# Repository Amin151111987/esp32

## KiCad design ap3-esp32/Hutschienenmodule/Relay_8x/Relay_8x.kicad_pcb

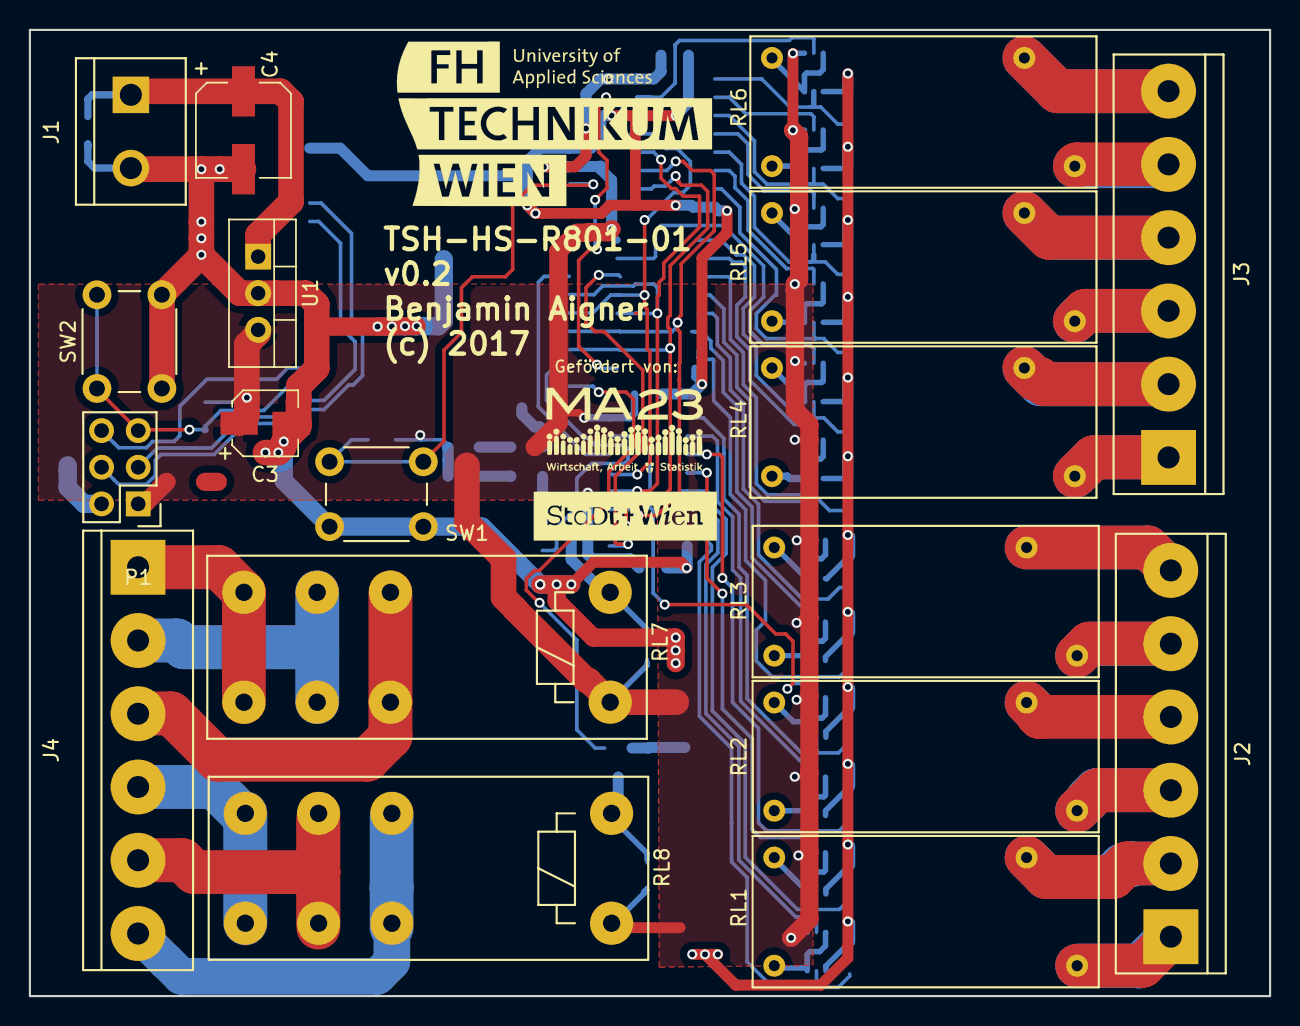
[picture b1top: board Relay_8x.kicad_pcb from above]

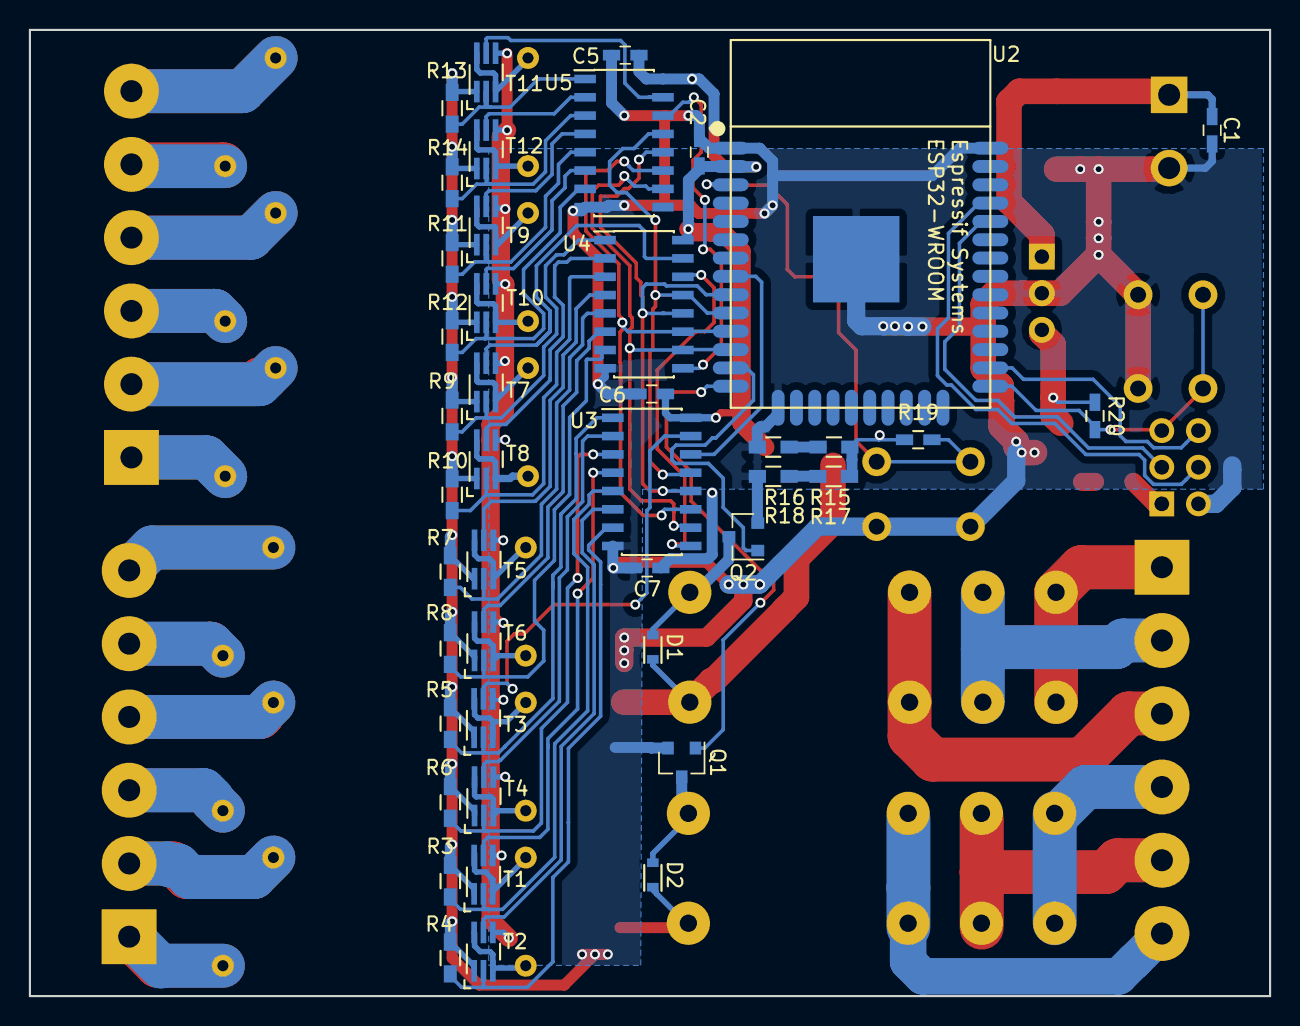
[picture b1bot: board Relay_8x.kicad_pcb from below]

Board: 2 copper layers, 86.0 x 67.0 mm, 61 parts (43 on the bottom side), 75 nets.

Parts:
C1, C2, C5, C6, C7: 100nF; C_0603_HandSoldering
C3: 22uF; CP_Elec_4x5.7
C4: 10uF; CP_Elec_6.3x5.8
D1, D2: D; D_0603
J1: Screw_Terminal_1x02; bornier2
J2, J3, J4: Screw_Terminal_1x06; bornier6
P1: CONN_02X03; Pin_Header_Straight_2x03
Q1, Q2: MMBF170; SOT-23
R3, R4, R5, R6, R7, R8, R9, R10, R11, R12, R13, R14: R_Small; R_0603_HandSoldering
R15, R16, R17, R18: R; R_0603_HandSoldering
R19, R20: 10k; C_0603_HandSoldering
RL1, RL2, RL3, RL4, RL5, RL6: ADW1103; ADW11
RL7, RL8: OZ-SS-103LM1; Relay_SPDT_Schrack-RT1_RM5mm
SW1, SW2: SW_Push; SW_PUSH_6mm_h7.3mm
T1, T2, T3, T4, T5, T6, T7, T8, T9, T10, T11, T12: NX3008CBKS; SC-70-6_Handsoldering
U1: TR10S3V3; TO-220_Vertical
U2: ESP32-WROOM
U3, U4, U5: 74HC595; SOIC-16_3.9x9.9mm_Pitch1.27mm

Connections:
1A1: RL1.A1, T1.3, T1.6
1A2: RL1.A2, T2.3, T2.6
2A1: RL2.A1, T3.3, T3.6
2A2: RL2.A2, T4.3, T4.6
3A1: RL3.A1, T5.3, T5.6
3A2: RL3.A2, T6.3, T6.6
4A1: RL4.A1, T7.3, T7.6
4A2: RL4.A2, T8.3, T8.6
5A1: RL5.A1, T9.3, T9.6
5A2: RL5.A2, T10.3, T10.6
6A1: RL6.A1, T11.3, T11.6
6A2: RL6.A2, T12.3, T12.6
7A2: D1.2, Q2.3, RL7.A2
8A2: D2.2, Q1.3, RL8.A2
+12V: C1.1, C4.1, J1.1, U1.1
/1G1H: T1.5, U3.4
/1G1L: R3.1, T1.2, U3.5
/1G2H: T2.5, U3.6
/1G2L: R4.1, T2.2, U3.7
/2G1H: T3.5, U3.15
/2G1L: R5.1, T3.2, U3.1
/2G2H: T4.5, U3.2
/2G2L: R6.1, T4.2, U3.3
/3G1H: T5.5, U4.4
/3G1L: R7.1, T5.2, U4.5
/3G2H: T6.5, U4.6
/3G2L: R8.1, T6.2, U4.7
/4G1H: T7.5, U4.15
/4G1L: R9.1, T7.2, U4.1
/4G2H: T8.5, U4.2
/4G2L: R10.1, T8.2, U4.3
/5G1H: T9.5, U5.4
/5G1L: R11.1, T9.2, U5.5
/5G2H: T10.5, U5.6
/5G2L: R12.1, T10.2, U5.7
/6G1H: T11.5, U5.15
/6G1L: R13.1, T11.2, U5.1
/6G2H: T12.5, U5.2
/6G2L: R14.1, T12.2, U5.3
/7G: Q2.1, U2.13
/8G: Q1.1, U2.14
/DIO0: P1.5, R20.2, SW2.1, U2.25
/DIO4: P1.6, U2.26
/G: U2.10, U3.13, U4.13, U5.13
/RCLK: U2.9, U3.12, U4.12, U5.12
/RXD: P1.3, U2.34
/SER: U2.8, U3.14
/SRCLK: U2.11, U3.11, U4.11, U5.11
/SRCLR: U2.12, U3.10, U4.10, U5.10
/TXD: P1.4, U2.35
GND: C1.2, C2.2, C3.2, C4.2, C5.2, C6.2, C7.2, J1.2, P1.2, Q1.2, Q2.2, R3.2, R4.2, R5.2, R6.2, R7.2, R8.2, R9.2, R10.2, R11.2, R12.2, R13.2, R14.2, R16.2, R18.2, SW1.1, SW2.2, T1.1, T2.1, T3.1, T4.1, T5.1, T6.1, T7.1, T8.1, T9.1, T10.1, T11.1, T12.1, U1.2, U2.1, U2.15, U2.38, U2.39, U3.8, U4.8, U5.8
unnamed: J2.1, RL1.14
unnamed: J2.2, RL1.11
unnamed: J2.3, RL2.14
unnamed: J2.4, RL2.11
unnamed: J2.5, RL3.14
unnamed: J2.6, RL3.11
unnamed: J3.1, RL4.14
unnamed: J3.2, RL4.11
unnamed: J3.3, RL5.14
unnamed: J3.4, RL5.11
unnamed: J3.5, RL6.14
unnamed: J3.6, RL6.11
unnamed: J4.1, RL7.14
unnamed: J4.2, RL7.11
unnamed: J4.3, RL7.12
unnamed: J4.4, RL8.14
unnamed: J4.5, RL8.11
unnamed: J4.6, RL8.12
unnamed: R15.2, R16.1
unnamed: R17.2, R18.1
unnamed: R19.2, SW1.2, U2.3
unnamed: U3.9, U4.14
unnamed: U4.9, U5.14
VCC: C2.1, C3.1, C5.1, C6.1, C7.1, D1.1, D2.1, P1.1, R15.1, R17.1, R19.1, R20.1, RL7.A1, RL8.A1, T1.4, T2.4, T3.4, T4.4, T5.4, T6.4, T7.4, T8.4, T9.4, T10.4, T11.4, T12.4, U1.3, U2.2, U3.16, U4.16, U5.16

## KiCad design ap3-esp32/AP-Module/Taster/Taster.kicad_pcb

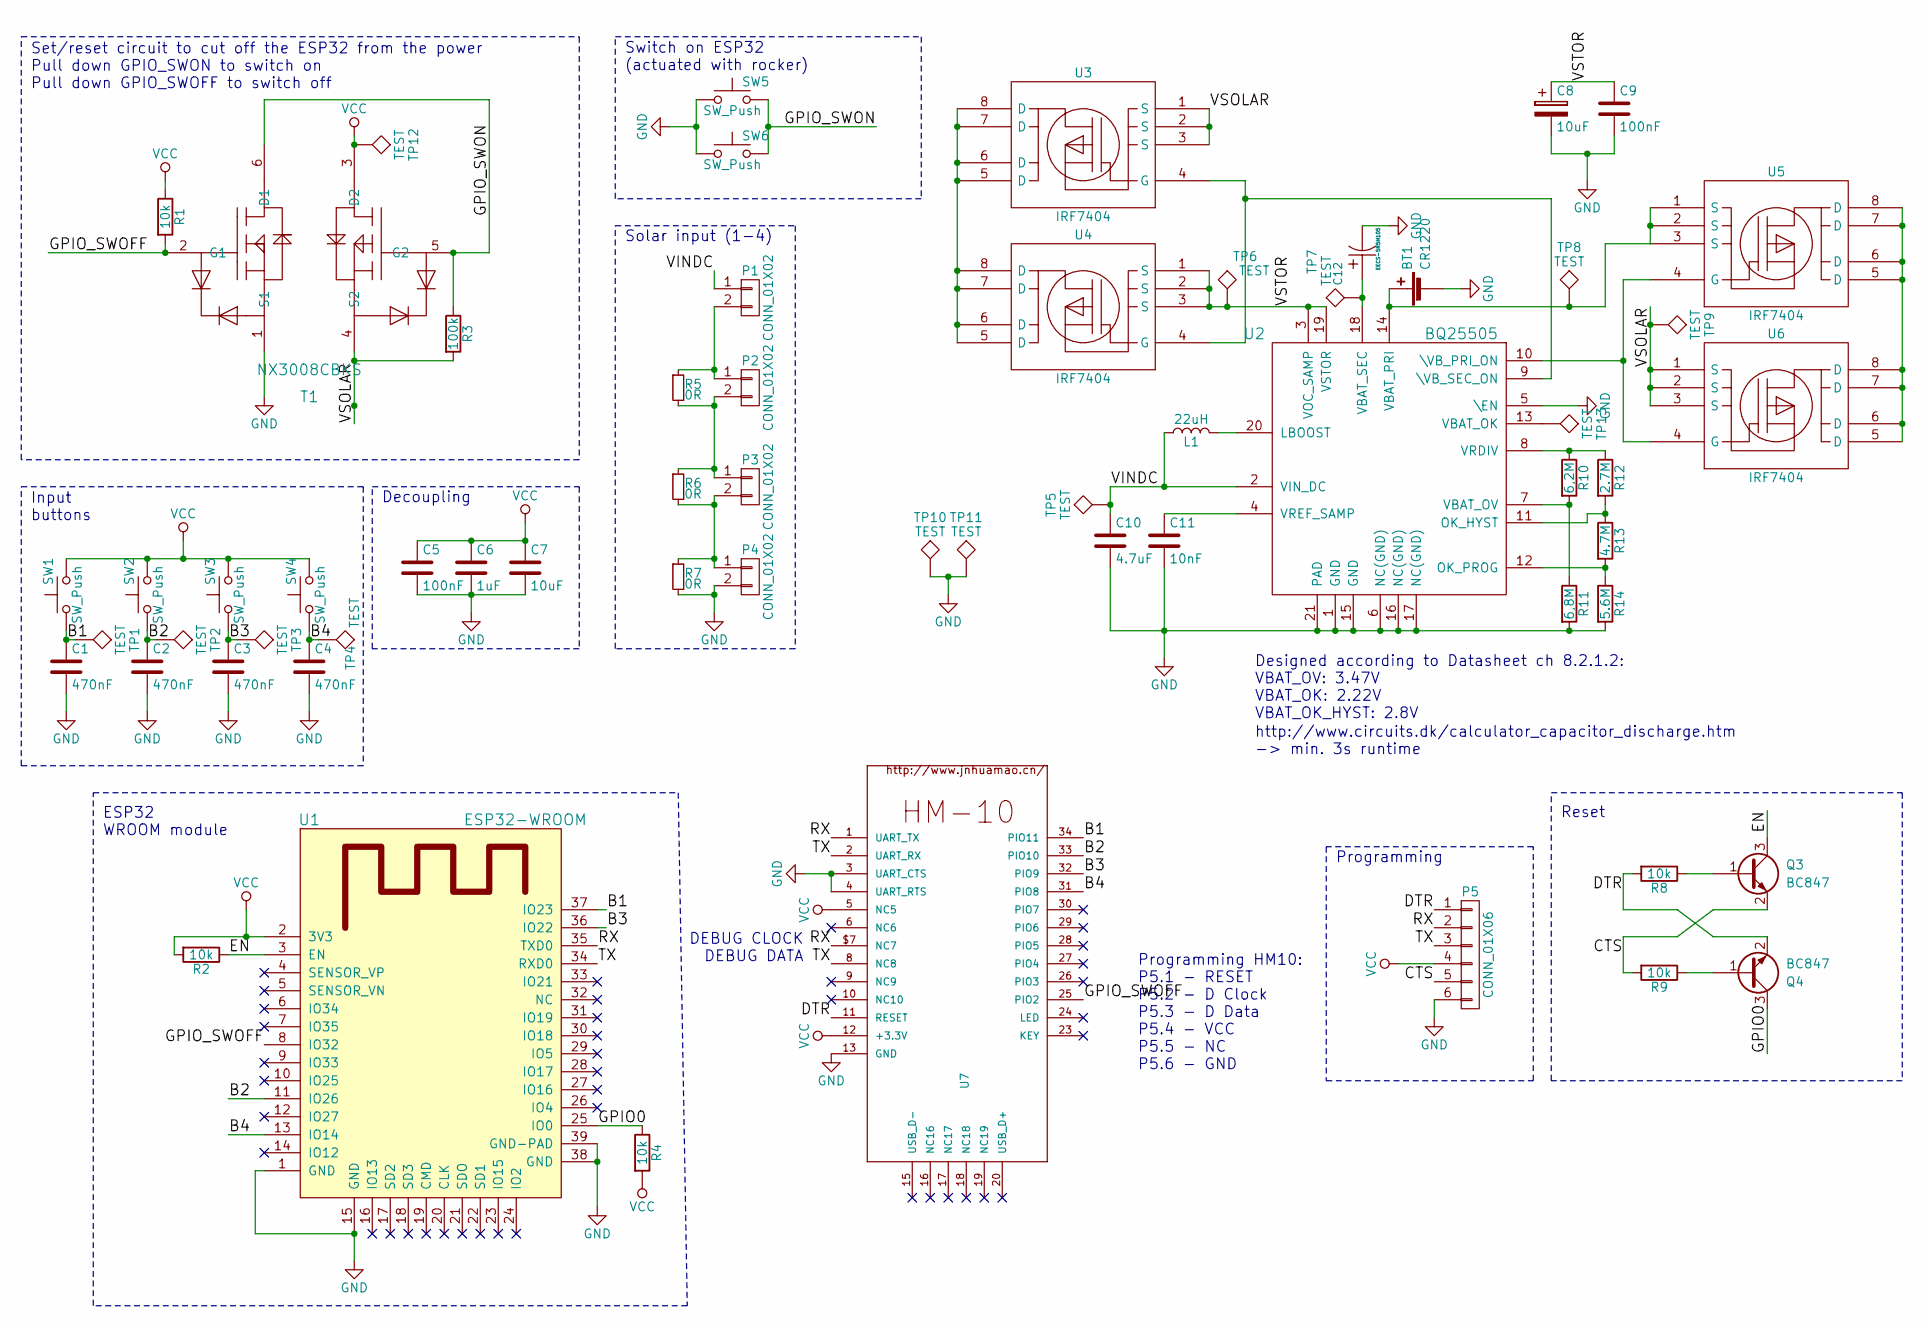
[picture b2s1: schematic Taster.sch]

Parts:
BT1: CR1220; CR2032H1.2
C1, C2, C3, C4: 470nF; C_0603
C5, C9: 100nF; C_0603
C6: 1uF; C_0603
C7, C8: 10uF; C_0805
C10: 4.7uF; C_0805
C11: 10nF; C_0603
C12: EECS-5R5H105; Panasonic-EEC-EECR-EECF-EECS-CAP_EECS5R5H
L1: 22uH; Choke_SMD_Wuerth-WE-PD2-Typ-MS
P1, P2, P3, P4: CONN_01X02; GS2
P5: CONN_01X06; Pin_Header_Straight_1x06
Q3, Q4: BC847; SOT-23
R1, R2, R4, R8, R9: 10k; R_0603
R3: 100k; R_0603
R5, R6, R7: 0R; R_0603
R10: 6,2M; R_0603
R11: 6,8M; R_0603
R12: 2.7M; R_0603
R13: 4.7M; R_0603
R14: 5.6M; R_0603
SW1, SW2, SW3, SW4, SW5, SW6: SW_Push; SW_SPST_EVQQ2
T1: NX3008CBKS; SC-70-6
TP1, TP2, TP3, TP4, TP5, TP6, TP7, TP8, TP9, TP10, TP11, TP12, TP13: TEST; PINTST
U1: ESP32-WROOM
U2: BQ25505; QFN-20-1EP_4x4mm_Pitch0.5mm
U3, U4, U5, U6: IRF7404; SO-8
U7: HM-10-BOARD; HM10

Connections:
/B1: C1.1, SW1.1, TP1.1, U1.37 (IO23), U7.34 (PIO11)
/B2: C2.1, SW2.1, TP2.1, U1.11 (IO26), U7.33 (PIO10)
/B3: C3.1, SW3.1, TP3.1, U1.36 (IO22), U7.32 (PIO9)
/B4: C4.1, SW4.1, TP4.1, U1.13 (IO14), U7.31 (PIO8)
/CTS: P5.5, Q3.2 (E), R9.2
/DTR: P5.1, Q4.2 (E), R8.2, U7.11 (RESET)
/EN: Q3.3 (C), R2.1, U1.3 (EN)
/GPIO0: Q4.3 (C), R4.1, U1.25 (IO0)
/GPIO_SWOFF: R1.2, T1.2 (G1), U1.8 (IO32), U7.25 (PIO2)
/GPIO_SWON: R3.1, SW5.2, SW6.2, T1.5 (G2), T1.6 (D1)
/RX: P5.2, U1.35 (TXD0), U7.1 (UART_TX), U7.$7 (NC7)
/TX: P5.3, U1.34 (RXD0), U7.2 (UART_RX), U7.8 (NC8)
/VINDC: C10.1, L1.1, P1.1, TP5.1, U2.2 (VIN_DC)
/VSOLAR: R3.2, T1.4 (S2), TP9.1, U3.1 (S), U3.2 (S), U3.3 (S), U6.1 (S), U6.2 (S), U6.3 (S)
/VSTOR: C8.1, C9.1, TP6.1, U2.3 (VOC_SAMP), U2.19 (VSTOR), U4.1 (S), U4.2 (S), U4.3 (S)
GND: BT1.2 (-), C1.2, C2.2, C3.2, C4.2, C5.2, C6.2, C7.2, C8.2, C9.2, C10.2, C11.2, C12.2, P4.2, P5.6, R7.2, R11.2, R14.2, SW5.1, SW6.1, T1.1 (S1), TP10.1, TP11.1, U1.1 (GND), U1.15 (GND), U1.38 (GND), U1.39 (GND-PAD), U2.1 (GND), U2.5 (\EN), U2.6 (NC(GND)), U2.15 (GND), U2.16 (NC(GND)), U2.17 (NC(GND)), U2.21 (PAD), U7.3 (UART_CTS), U7.4 (UART_RTS), U7.13 (GND), U7.14 (GND), U7.21 (GND), U7.22 (GND)
unnamed: BT1.1 (+), TP8.1, U2.14 (VBAT_PRI), U5.1 (S), U5.2 (S), U5.3 (S)
unnamed: C11.1, U2.4 (VREF_SAMP)
unnamed: C12.1, TP7.1, U2.18 (VBAT_SEC)
unnamed: L1.2, U2.20 (LBOOST)
unnamed: P1.2, P2.1, R5.1
unnamed: P2.2, P3.1, R5.2, R6.1
unnamed: P3.2, P4.1, R6.2, R7.1
unnamed: Q3.1 (B), R8.1
unnamed: Q4.1 (B), R9.1
unnamed: R10.1, R12.1, U2.8 (VRDIV)
unnamed: R10.2, R11.1, U2.7 (VBAT_OV)
unnamed: R12.2, R13.1, U2.11 (OK_HYST)
unnamed: R13.2, R14.1, U2.12 (OK_PROG)
unnamed: TP13.1, U2.13 (VBAT_OK)
unnamed: U2.9 (\VB_SEC_ON), U3.4 (G), U4.4 (G)
unnamed: U2.10 (\VB_PRI_ON), U5.4 (G), U6.4 (G)
unnamed: U3.5 (D), U3.6 (D), U3.7 (D), U3.8 (D), U4.5 (D), U4.6 (D), U4.7 (D), U4.8 (D)
unnamed: U5.5 (D), U5.6 (D), U5.7 (D), U5.8 (D), U6.5 (D), U6.6 (D), U6.7 (D), U6.8 (D)
VCC: C5.1, C6.1, C7.1, P5.4, R1.1, R2.2, R4.2, SW1.2, SW2.2, SW3.2, SW4.2, T1.3 (D2), TP12.1, U1.2 (3V3), U7.5 (NC5), U7.12 (+3.3V)

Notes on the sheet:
Set/reset circuit to cut off the ESP32 from the power Pull down GPIO_SWON to switch on Pull down GPIO_SWOFF to switch off
Switch on ESP32 (actuated with rocker)
Input buttons
Decoupling
Solar input (1-4)
Programming
Reset
ESP32 WROOM module
Designed according to Datasheet ch 8.2.1.2: VBAT_OV: 3.47V VBAT_OK: 2.22V VBAT_OK_HYST: 2.8V
http://www.circuits.dk/calculator_capacitor_discharge.htm -> min. 3s runtime
DEBUG CLOCK DEBUG DATA
Programming HM10: P5.1 - RESET P5.2 - D Clock P5.3 - D Data P5.4 - VCC P5.5 - NC P5.6 - GND

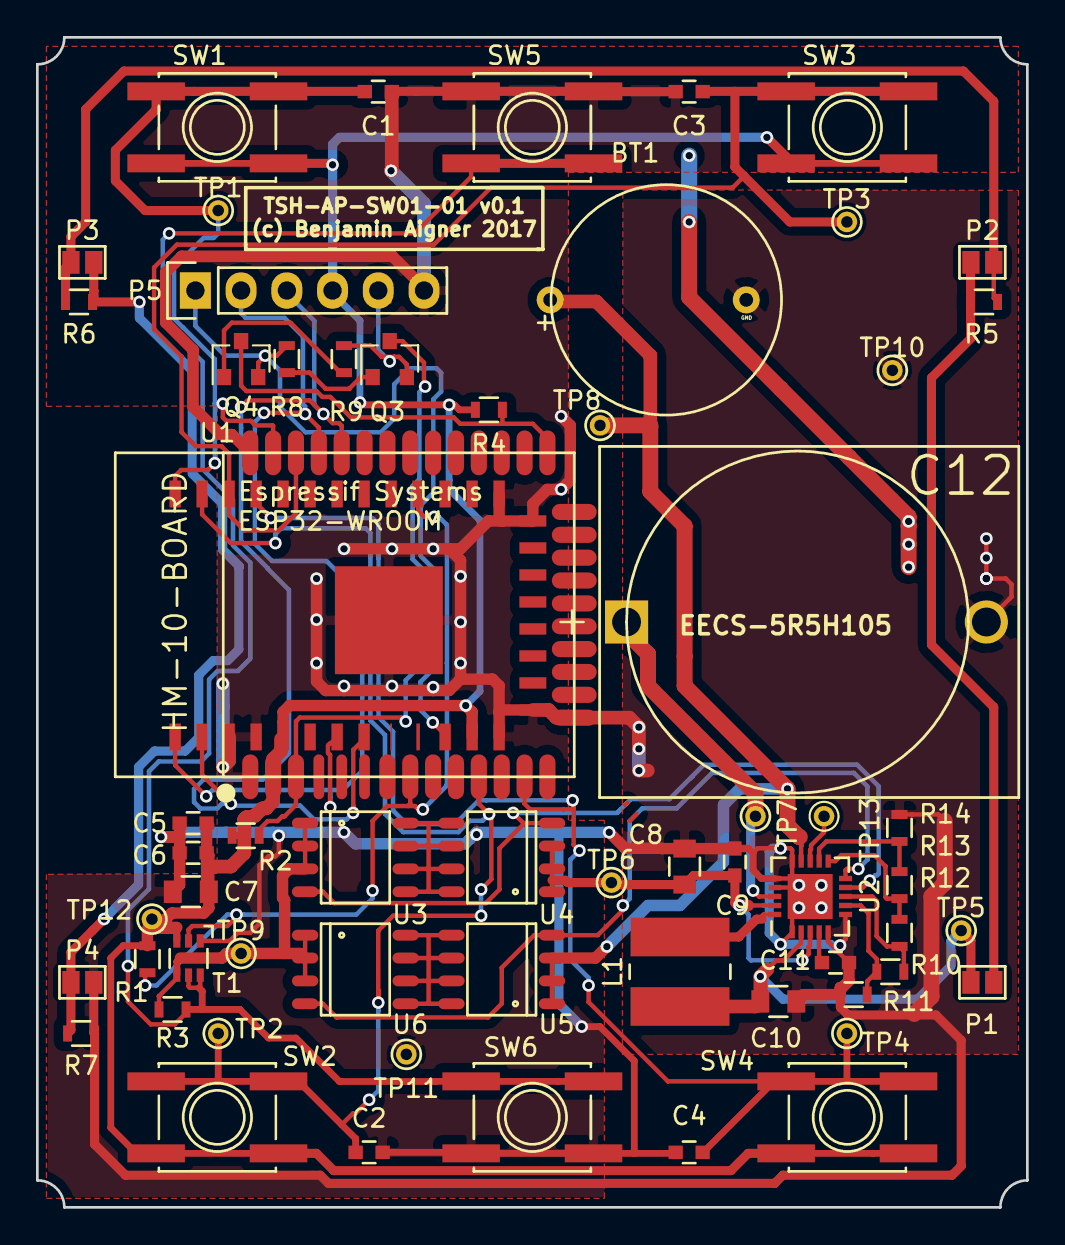
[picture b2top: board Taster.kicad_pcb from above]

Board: 2 copper layers, 55.0 x 65.0 mm, 62 parts (0 on the bottom side), 35 nets.

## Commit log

2017-11-10 Erster Commit !

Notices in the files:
ap3-esp32/Hutschienenmodule/Relay_8x/Relay_8x.kicad_pcb:
(c) 2017
